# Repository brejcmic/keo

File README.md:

# B0B13KEO

- materiály, 
- prezentace

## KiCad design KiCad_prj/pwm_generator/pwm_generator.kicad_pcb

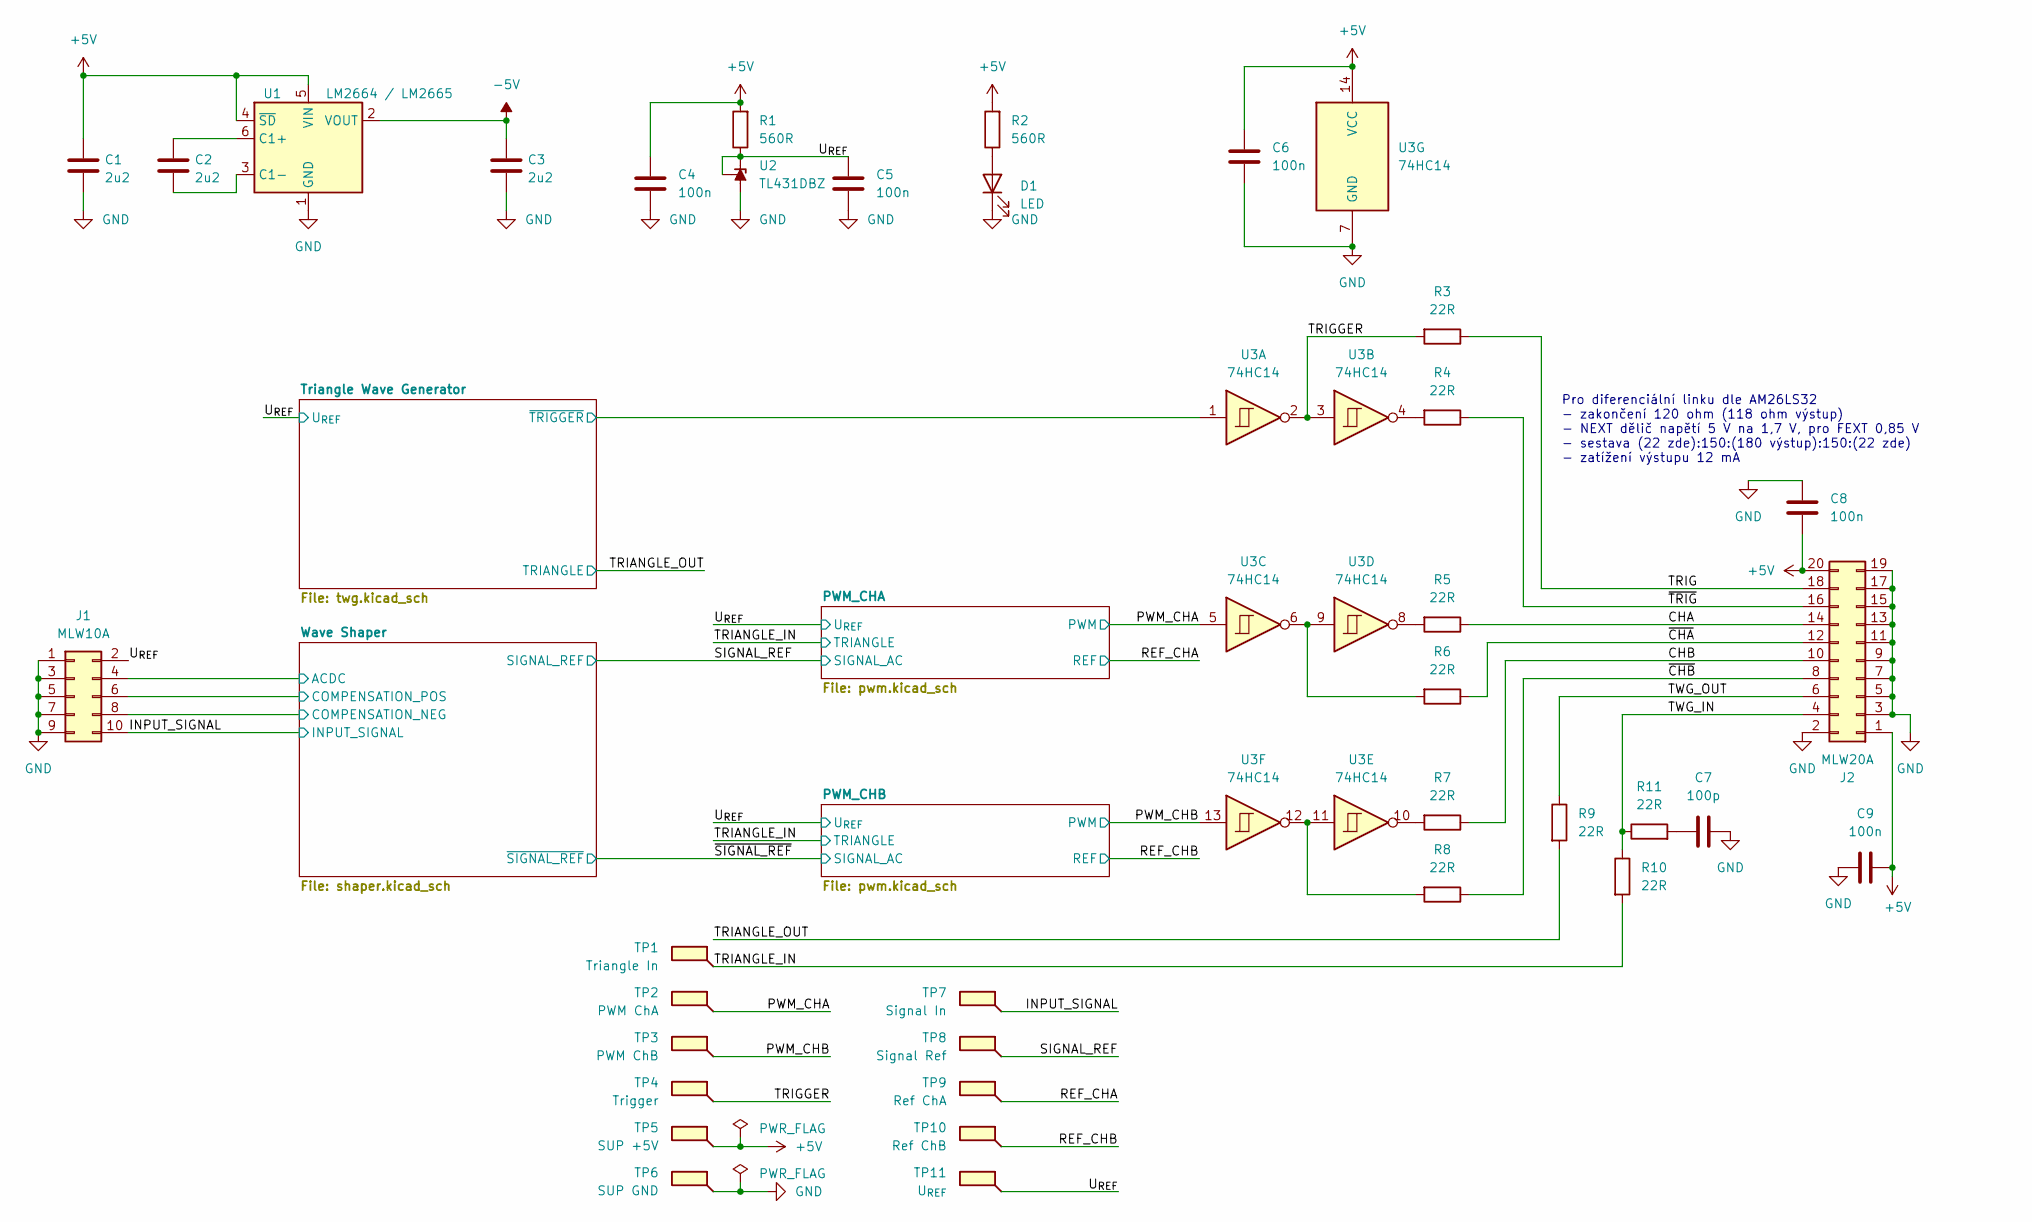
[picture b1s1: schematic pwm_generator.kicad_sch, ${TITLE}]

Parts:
C1, C2, C3: 2u2; C_0805_2012Metric; JLCPCB Part # C377773
C4, C5, C6, C8, C9: 100n; C_0805_2012Metric; JLCPCB Part # C49678
C7: 100p; C_0805_2012Metric; JLCPCB Part # C1790
D1: LED; LED_0805_2012Metric; JLCPCB Part # C84256
J1: MLW10A; IDC-Header_2x05_P2.54mm_Horizontal
J2: MLW20A; IDC-Header_2x10_P2.54mm_Horizontal
R1, R2: 560R; R_0805_2012Metric; JLCPCB Part # C28636
R3, R4, R5, R6, R7, R8, R9, R10, R11: 22R; R_0805_2012Metric; JLCPCB Part # C17561
TP1: Triangle In; TestPoint_Loop_D1.80mm_Drill1.0mm_Beaded
TP2: PWM ChA; TestPoint_Loop_D1.80mm_Drill1.0mm_Beaded
TP3: PWM ChB; TestPoint_Loop_D1.80mm_Drill1.0mm_Beaded
TP4: Trigger; TestPoint_Loop_D1.80mm_Drill1.0mm_Beaded
TP5: SUP +5V; TestPoint_Loop_D1.80mm_Drill1.0mm_Beaded
TP6: SUP GND; TestPoint_Loop_D1.80mm_Drill1.0mm_Beaded
TP7: Signal In; TestPoint_Loop_D1.80mm_Drill1.0mm_Beaded
TP8: Signal Ref; TestPoint_Loop_D1.80mm_Drill1.0mm_Beaded
TP9: Ref ChA; TestPoint_Loop_D1.80mm_Drill1.0mm_Beaded
TP10: Ref ChB; TestPoint_Loop_D1.80mm_Drill1.0mm_Beaded
TP11: U_{REF}; TestPoint_Loop_D1.80mm_Drill1.0mm_Beaded
U1: LM2664 / LM2665; SOT-23-6; JLCPCB Part # C840095
U2: TL431DBZ; SOT-23; JLCPCB Part # C181103
U3: 74HC14; SOIC-14_3.9x8.7mm_P1.27mm; JLCPCB Part # C5605

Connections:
+5V: C1.1, C4.2, C6.2, C8.2, C9.2, J2.1, J2.20, R1.2, R2.2, TP5.1 (1_1), U1.4 (~SD), U1.5 (VIN), U3.14 (VCC); also elsewhere on the board
-5V: C3.1, U1.2 (VOUT); also elsewhere on the board
/CHA: J2.14, R5.1
/CHB: J2.10, R7.1
/INPUT_SIGNAL: J1.10, TP7.1 (1_1); also elsewhere on the board
/PWM_CHA: TP2.1 (1_1), U3.5; also elsewhere on the board
/PWM_CHB: TP3.1 (1_1), U3.13; also elsewhere on the board
/REF_CHA: TP9.1 (1_1); also elsewhere on the board
/REF_CHB: TP10.1 (1_1); also elsewhere on the board
/SIGNAL_REF: TP8.1 (1_1); also elsewhere on the board
/TRIANGLE_IN: R10.2, TP1.1 (1_1); also elsewhere on the board
/TRIANGLE_OUT: R9.2; also elsewhere on the board
/TRIG: J2.18, R3.1
/TRIGGER: R3.2, TP4.1 (1_1), U3.2, U3.3
/TWG_IN: J2.4, R10.1, R11.1
/TWG_OUT: J2.6, R9.1
/Triangle Wave Generator/~TRIGGER: U3.1; also elsewhere on the board
/U_{REF}: C5.2, J1.2, R1.1, TP11.1 (1_1), U2.1 (K), U2.2 (REF); also elsewhere on the board
/Wave Shaper/ACDC: J1.4; also elsewhere on the board
/Wave Shaper/COMPENSATION_NEG: J1.8; also elsewhere on the board
/Wave Shaper/COMPENSATION_POS: J1.6; also elsewhere on the board
/~CHA: J2.12, R6.1
/~CHB: J2.8, R8.1
/~TRIG: J2.16, R4.1
GND: C1.2, C3.2, C4.1, C5.1, C6.1, C7.2, C8.1, C9.1, D1.1 (K), J1.1, J1.3, J1.5, J1.7, J1.9, J2.2, J2.3, J2.5, J2.7, J2.9, J2.11, J2.13, J2.15, J2.17, J2.19, TP6.1 (1_1), U1.1 (GND), U2.3 (A), U3.7 (GND); also elsewhere on the board
unnamed: C7.1, R11.2
unnamed: D1.2 (A), R2.1
unnamed: R4.2, U3.4
unnamed: R5.2, U3.8
unnamed: R6.2, U3.6, U3.9
unnamed: R7.2, U3.10
unnamed: R8.2, U3.11, U3.12
unnamed: C2.1, U1.6 (C1+)
unnamed: C2.2, U1.3 (C1-)

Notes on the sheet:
Pro diferenciální linku dle AM26LS32 - zakončení 120 ohm (118 ohm výstup) - NEXT dělič napětí 5 V na 1,7 V, pro FEXT 0,85 V - sestava (22 zde):150:(180 výstup):150:(22 zde) - zatížení výstupu 12 mA

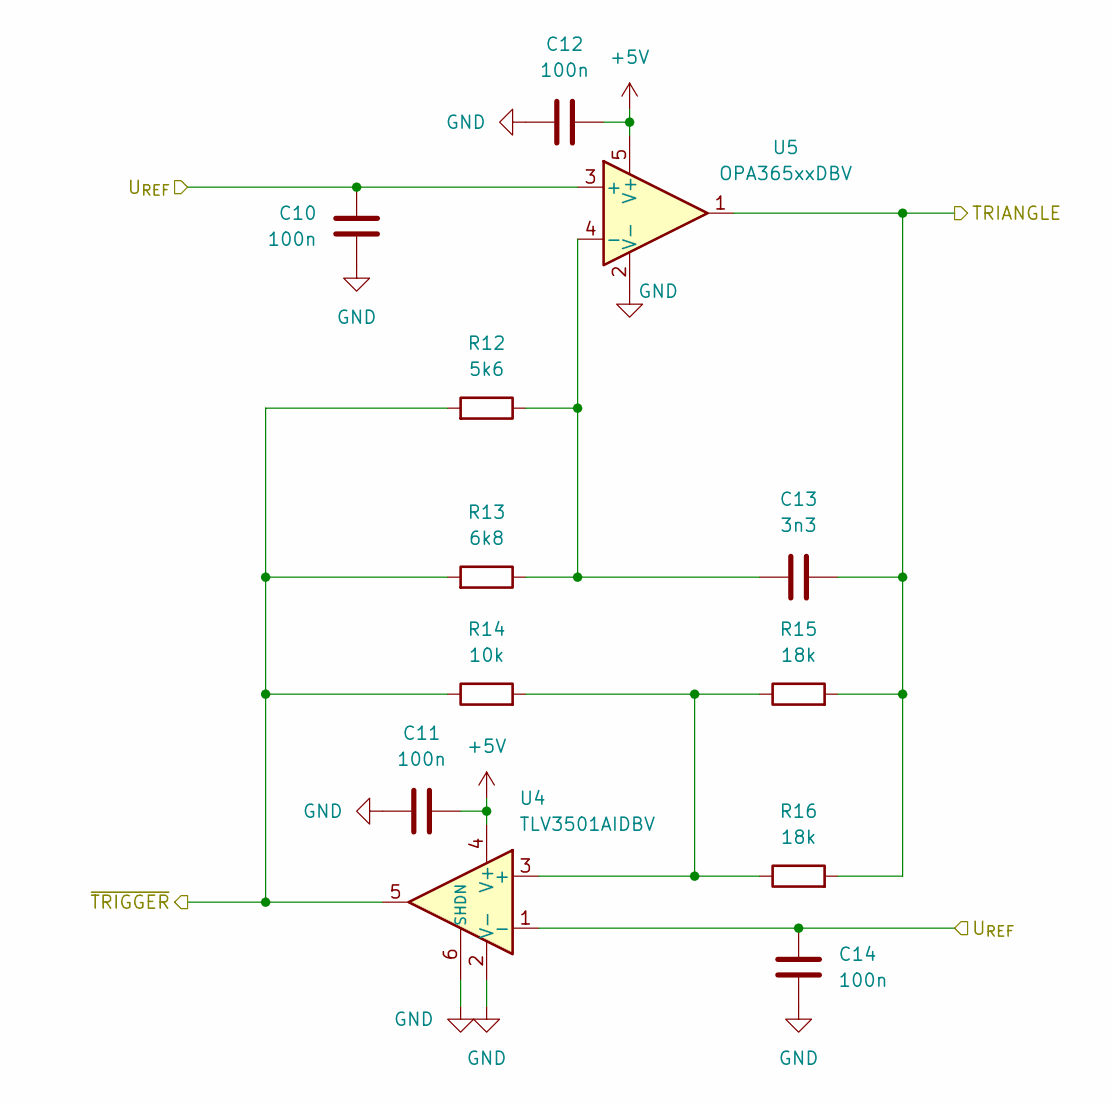
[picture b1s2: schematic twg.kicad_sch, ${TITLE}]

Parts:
C10, C11, C12, C14: 100n; C_0805_2012Metric; JLCPCB Part # C49678
C13: 3n3; C_0805_2012Metric; JLCPCB Part # C7467177
R12: 5k6; R_0805_2012Metric; JLCPCB Part # C4382
R13: 6k8; R_0805_2012Metric; JLCPCB Part # C17772
R14: 10k; R_0805_2012Metric; JLCPCB Part # C17414
R15, R16: 18k; R_0805_2012Metric; JLCPCB Part # C17506
U4: TLV3501AIDBV; SOT-23-6; JLCPCB Part # C193413
U5: OPA365xxDBV; SOT-23-5; JLCPCB Part # C96626

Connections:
+5V: C11.2, C12.2, U4.4 (V+), U5.5 (V+); also elsewhere on the board
/TRIANGLE_OUT: C13.2, R15.2, R16.2, U5.1; also elsewhere on the board
/Triangle Wave Generator/~TRIGGER: R12.2, R13.2, R14.1, U4.5; also elsewhere on the board
/U_{REF}: C10.2, C14.2, U4.1 (-), U5.3 (+); also elsewhere on the board
GND: C10.1, C11.1, C12.1, C14.1, U4.2 (V-), U4.6 (SHDN), U5.2 (V-); also elsewhere on the board
unnamed: R14.2, R15.1, R16.1, U4.3 (+)
unnamed: C13.1, R12.1, R13.1, U5.4 (-)

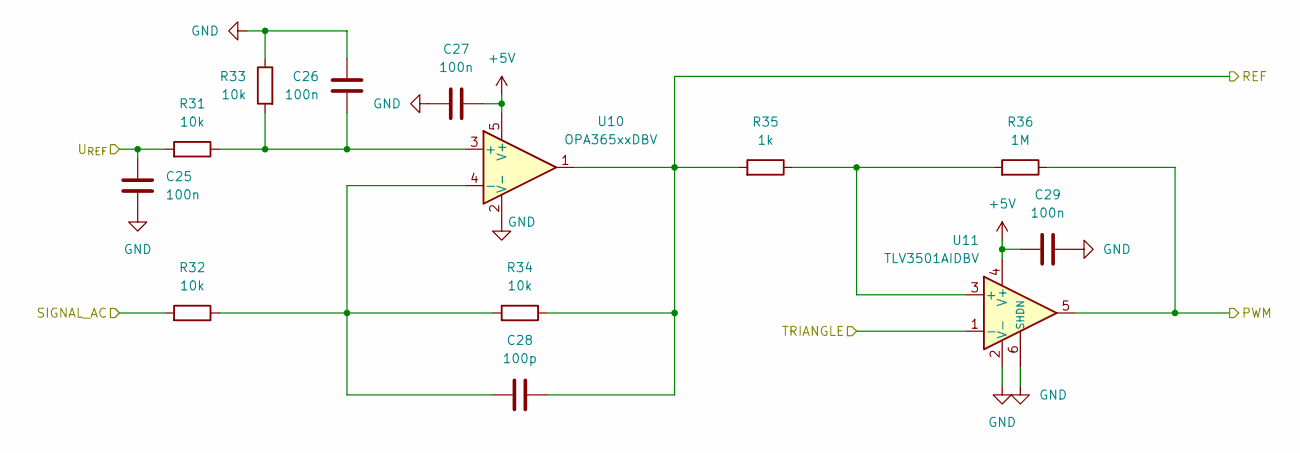
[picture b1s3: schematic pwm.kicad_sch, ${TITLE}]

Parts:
C25, C26, C27, C29: 100n; C_0805_2012Metric; JLCPCB Part # C49678
C28: 100p; C_0805_2012Metric; JLCPCB Part # C1790
R31, R32, R33, R34: 10k; R_0805_2012Metric; JLCPCB Part # C17414
R35: 1k; R_0805_2012Metric; JLCPCB Part # C17513
R36: 1M; R_0805_2012Metric; JLCPCB Part # C17514
U10: OPA365xxDBV; SOT-23-5; JLCPCB Part # C96626
U11: TLV3501AIDBV; SOT-23-6; JLCPCB Part # C193413

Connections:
+5V: C27.2, C29.2, U10.5 (V+), U11.4 (V+); also elsewhere on the board
/PWM_CHA: R36.1, U11.5; also elsewhere on the board
/REF_CHA: C28.2, R34.1, R35.2, U10.1; also elsewhere on the board
/SIGNAL_REF: R32.2; also elsewhere on the board
/TRIANGLE_IN: U11.1 (-); also elsewhere on the board
/U_{REF}: C25.2, R31.2; also elsewhere on the board
GND: C25.1, C26.1, C27.1, C29.1, R33.1, U10.2 (V-), U11.2 (V-), U11.6 (SHDN); also elsewhere on the board
unnamed: C26.2, R31.1, R33.2, U10.3 (+)
unnamed: C28.1, R32.1, R34.2, U10.4 (-)
unnamed: R35.1, R36.2, U11.3 (+)

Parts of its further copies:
C30, C31, C32, C34: 100n; C_0805_2012Metric; JLCPCB Part # C49678
C33: 100p; C_0805_2012Metric; JLCPCB Part # C1790
R37, R38, R39, R40: 10k; R_0805_2012Metric; JLCPCB Part # C17414
R41: 1k; R_0805_2012Metric; JLCPCB Part # C17513
R42: 1M; R_0805_2012Metric; JLCPCB Part # C17514
U12: OPA365xxDBV; SOT-23-5; JLCPCB Part # C96626
U13: TLV3501AIDBV; SOT-23-6; JLCPCB Part # C193413

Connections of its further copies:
+5V: C32.2, C34.2, U12.5 (V+), U13.4 (V+); also elsewhere on the board
/PWM_CHB: R42.1, U13.5; also elsewhere on the board
/REF_CHB: C33.2, R40.1, R41.2, U12.1; also elsewhere on the board
/TRIANGLE_IN: U13.1 (-); also elsewhere on the board
/U_{REF}: C30.2, R37.2; also elsewhere on the board
/~SIGNAL_REF: R38.2; also elsewhere on the board
GND: C30.1, C31.1, C32.1, C34.1, R39.1, U12.2 (V-), U13.2 (V-), U13.6 (SHDN); also elsewhere on the board
unnamed: C31.2, R37.1, R39.2, U12.3 (+)
unnamed: C33.1, R38.1, R40.2, U12.4 (-)
unnamed: R41.1, R42.2, U13.3 (+)

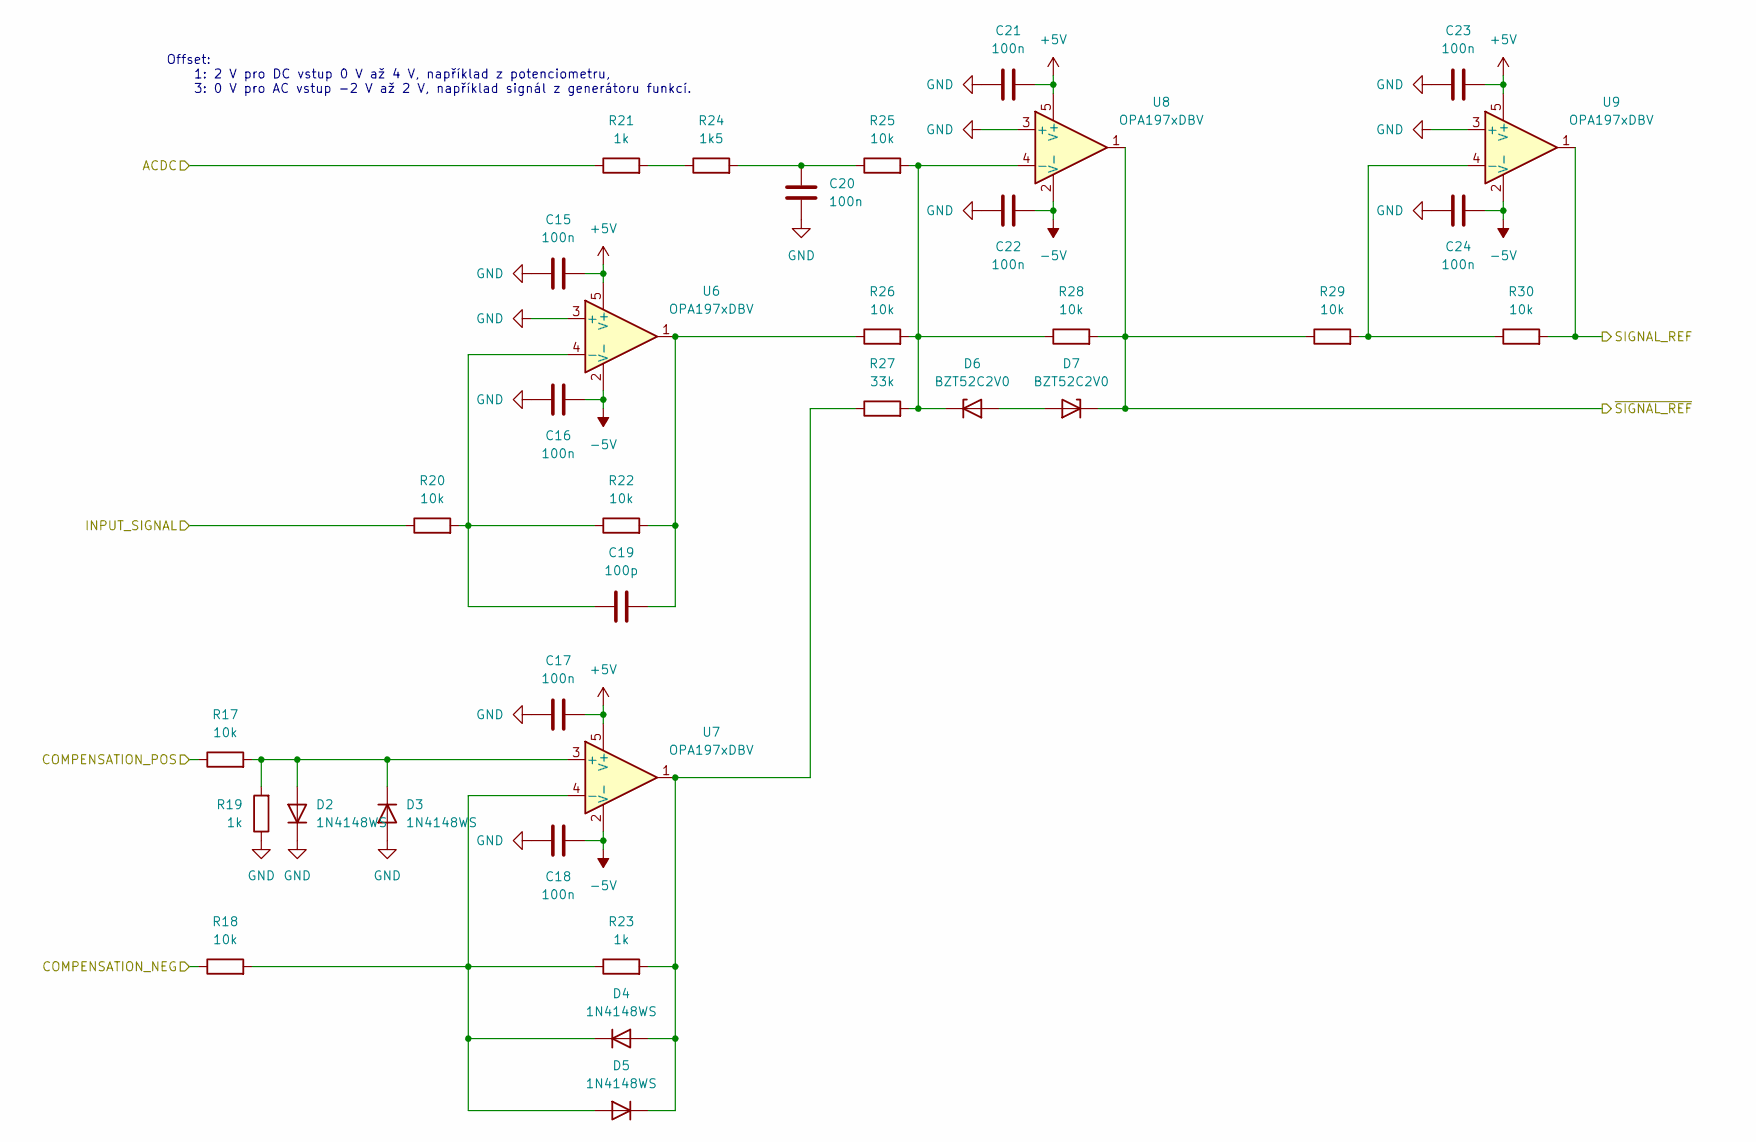
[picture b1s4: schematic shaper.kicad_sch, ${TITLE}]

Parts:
C15, C16, C17, C18, C20, C21, C22, C23, C24: 100n; C_0805_2012Metric; JLCPCB Part # C49678
C19: 100p; C_0805_2012Metric; JLCPCB Part # C1790
D2, D3, D4, D5: 1N4148WS; D_SOD-323; JLCPCB Part # C2128
D6, D7: BZT52C2V0; D_SOD-123F; JLCPCB Part # C41410795
R17, R18, R20, R22, R25, R26, R28, R29, R30: 10k; R_0805_2012Metric; JLCPCB Part # C17414
R19, R21, R23: 1k; R_0805_2012Metric; JLCPCB Part # C17513
R24: 1k5; R_0805_2012Metric; JLCPCB Part # C4310
R27: 33k; R_0805_2012Metric; JLCPCB Part # C17633
U6, U7, U8, U9: OPA197xDBV; SOT-23-5; JLCPCB Part # C221351

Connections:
+5V: C15.2, C17.2, C21.2, C23.2, U6.5 (V+), U7.5 (V+), U8.5 (V+), U9.5 (V+); also elsewhere on the board
-5V: C16.2, C18.2, C22.2, C24.2, U6.2 (V-), U7.2 (V-), U8.2 (V-), U9.2 (V-); also elsewhere on the board
/INPUT_SIGNAL: R20.1; also elsewhere on the board
/SIGNAL_REF: R30.2, U9.1; also elsewhere on the board
/Wave Shaper/ACDC: R21.1; also elsewhere on the board
/Wave Shaper/COMPENSATION_NEG: R18.1; also elsewhere on the board
/Wave Shaper/COMPENSATION_POS: R17.1; also elsewhere on the board
/~SIGNAL_REF: D7.1 (K), R28.2, R29.1, U8.1; also elsewhere on the board
GND: C15.1, C16.1, C17.1, C18.1, C20.1, C21.1, C22.1, C23.1, C24.1, D2.1 (K), D3.2 (A), R19.1, U6.3 (+), U8.3 (+), U9.3 (+); also elsewhere on the board
unnamed: C19.2, R22.2, R26.1, U6.1
unnamed: C20.2, R24.2, R25.1
unnamed: D2.2 (A), D3.1 (K), R17.2, R19.2, U7.3 (+)
unnamed: D4.2 (A), D5.1 (K), R23.2, R27.1, U7.1
unnamed: D4.1 (K), D5.2 (A), R18.2, R23.1, U7.4 (-)
unnamed: D6.2 (A), D7.2 (A)
unnamed: D6.1 (K), R25.2, R26.2, R27.2, R28.1, U8.4 (-)
unnamed: R21.2, R24.1
unnamed: C19.1, R20.2, R22.1, U6.4 (-)
unnamed: R29.2, R30.1, U9.4 (-)

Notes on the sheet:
Offset: 1: 2 V pro DC vstup 0 V až 4 V, například z potenciometru, 3: 0 V pro AC vstup -2 V až 2 V, například signál z generátoru funkcí.

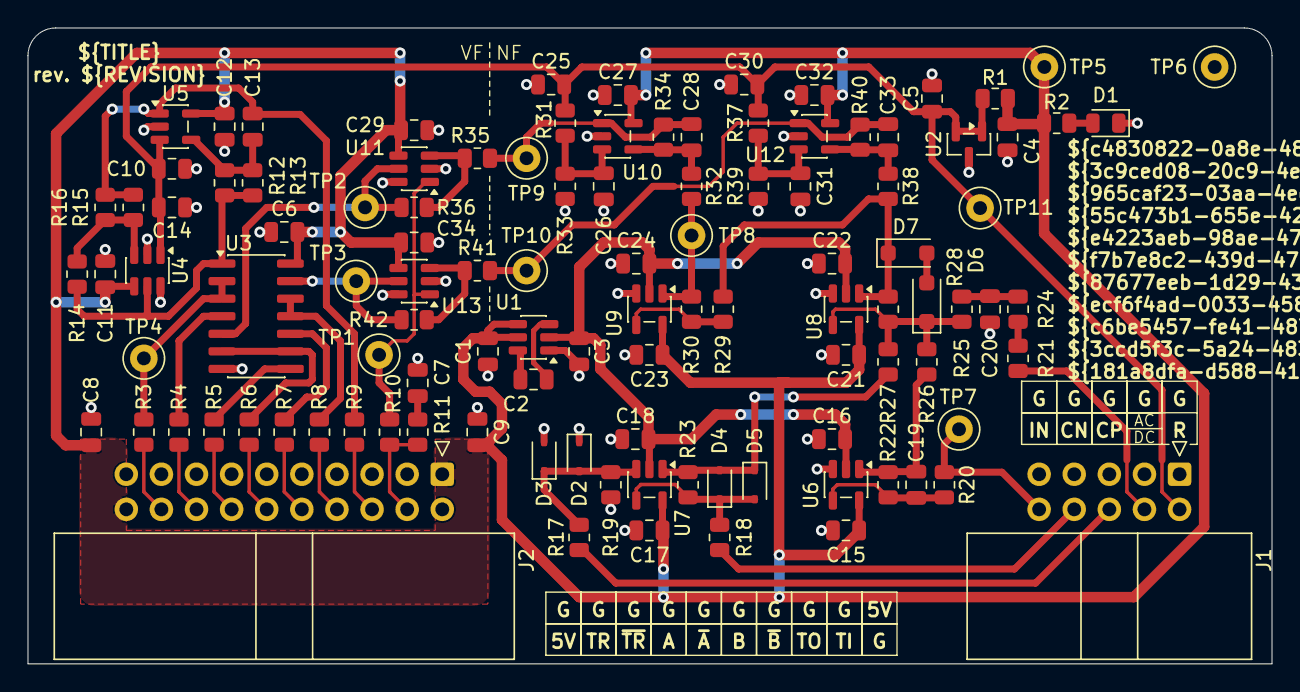
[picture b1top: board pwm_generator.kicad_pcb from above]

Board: 2 copper layers, 90.0 x 46.0 mm, 109 parts (0 on the bottom side), 53 nets.

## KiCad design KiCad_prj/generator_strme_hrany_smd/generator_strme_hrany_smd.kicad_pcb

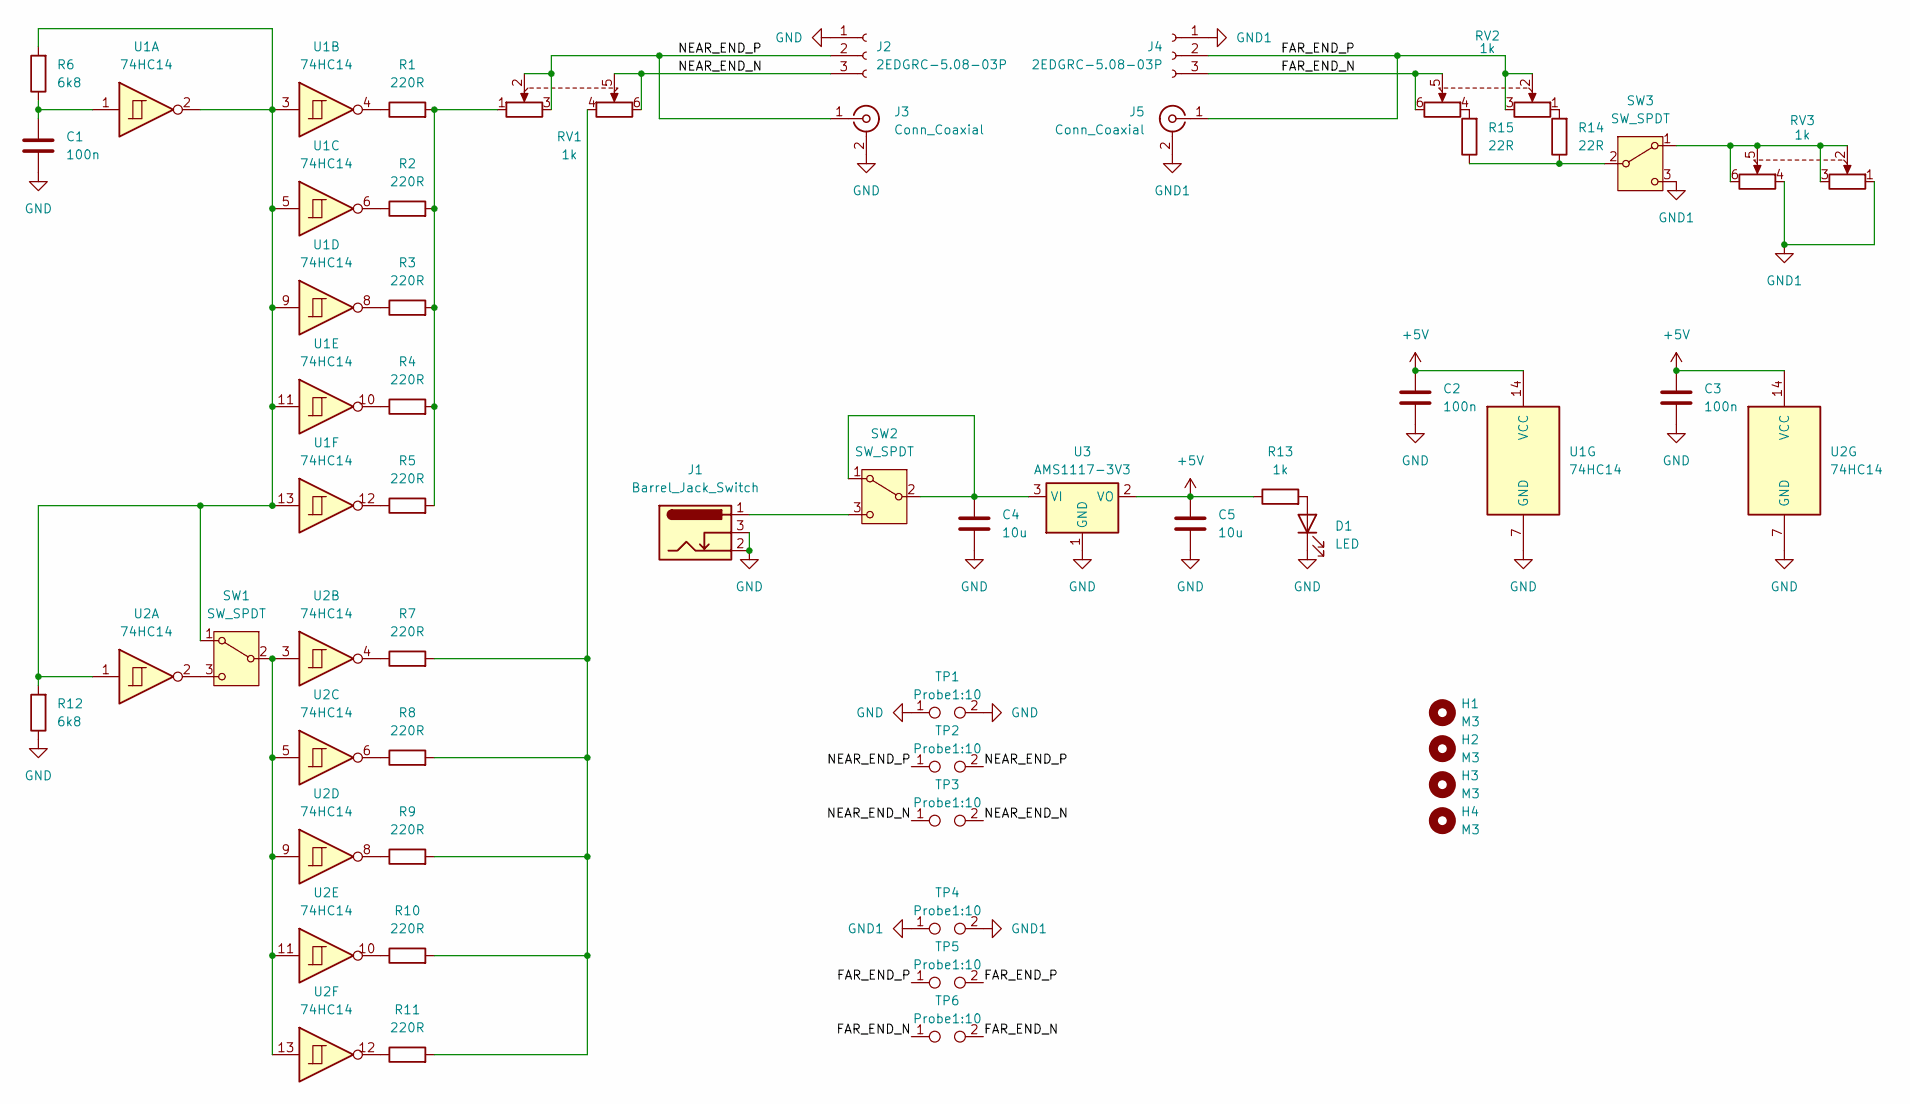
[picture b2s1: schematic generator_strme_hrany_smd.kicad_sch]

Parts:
C1, C2, C3: 100n; C_0805_2012Metric
C4, C5: 10u; C_0805_2012Metric
D1: LED; LED_0805_2012Metric
H1, H2, H3, H4: M3; MountingHole_3.2mm_M3_ISO7380
J1: Barrel_Jack_Switch; BarrelJack_GCT_DCJ200-10-A_Horizontal
J2, J4: 2EDGRC-5.08-03P; PhoenixContact_MSTBA_2,5_3-G-5,08_1x03_P5.08mm_Horizontal
J3, J5: Conn_Coaxial; BNC_Amphenol_B6252HB-NPP3G-50_Horizontal
R1, R2, R3, R4, R5, R7, R8, R9, R10, R11: 220R; R_0805_2012Metric
R6, R12: 6k8; R_0805_2012Metric
R13: 1k; R_0805_2012Metric
R14, R15: 22R; R_0805_2012Metric
RV1, RV2, RV3: 1k; Potentiometer_Alpha_RD902F-40-00D_Dual_Vertical
SW1, SW2, SW3: SW_SPDT; KLS7-SS02-12F20
TP1, TP2, TP3, TP4, TP5, TP6: Probe1:10; TestPoint_2Pads_Pitch2.54mm_Drill0.8mm
U1, U2: 74HC14; DIP-14_W7.62mm_LongPads
U3: AMS1117-3V3; SOT-223-3_TabPin2

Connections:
+5V: C2.1, C3.1, C5.1, R13.1, U1.14 (VCC), U2.14 (VCC), U3.2 (VO)
/FAR_END_N: J4.3, RV2.5, RV2.6, TP6.1, TP6.2
/FAR_END_P: J4.2, J5.1 (In), RV2.2, RV2.3, TP5.1, TP5.2
/NEAR_END_N: J2.3, RV1.5, RV1.6, TP3.1, TP3.2
/NEAR_END_P: J2.2, J3.1 (In), RV1.2, RV1.3, TP2.1, TP2.2
GND: C1.2, C2.2, C3.2, C4.2, C5.2, D1.1 (K), J1.2, J1.3, J2.1, J3.2 (Ext), R12.1, TP1.1, TP1.2, U1.7 (GND), U2.7 (GND), U3.1 (GND)
GND1: J4.1, J5.2 (Ext), RV3.1, RV3.4, SW3.3 (C), TP4.1, TP4.2
unnamed: C1.1, R6.1, U1.1
unnamed: D1.2 (A), R13.2
unnamed: R1.1, U1.4
unnamed: R1.2, R2.2, R3.2, R4.2, R5.2, RV1.1
unnamed: R2.1, U1.6
unnamed: R3.1, U1.8
unnamed: R4.1, U1.10
unnamed: R5.1, U1.12
unnamed: R7.1, U2.4
unnamed: R8.1, U2.6
unnamed: R9.1, U2.8
unnamed: R10.1, U2.10
unnamed: R7.2, R8.2, R9.2, R10.2, R11.2, RV1.4
unnamed: R11.1, U2.12
unnamed: R14.2, RV2.1
unnamed: R15.2, RV2.4
unnamed: R6.2, R12.2, SW1.1 (A), U1.2, U1.3, U1.5, U1.9, U1.11, U1.13, U2.1
unnamed: SW1.2 (B), U2.3, U2.5, U2.9, U2.11, U2.13
unnamed: SW1.3 (C), U2.2
unnamed: C4.1, SW2.1 (A), SW2.2 (B), U3.3 (VI)
unnamed: J1.1, SW2.3 (C)
unnamed: RV3.2, RV3.3, RV3.5, RV3.6, SW3.1 (A)
unnamed: R14.1, R15.1, SW3.2 (B)

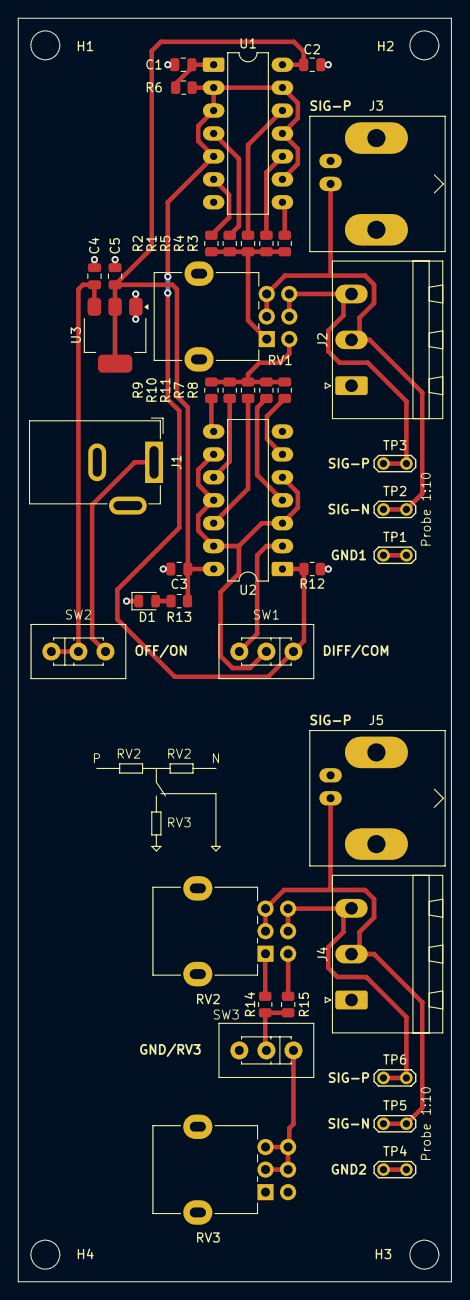
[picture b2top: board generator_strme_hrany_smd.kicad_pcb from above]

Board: 2 copper layers, 48.0 x 140.0 mm, 45 parts (0 on the bottom side), 30 nets.

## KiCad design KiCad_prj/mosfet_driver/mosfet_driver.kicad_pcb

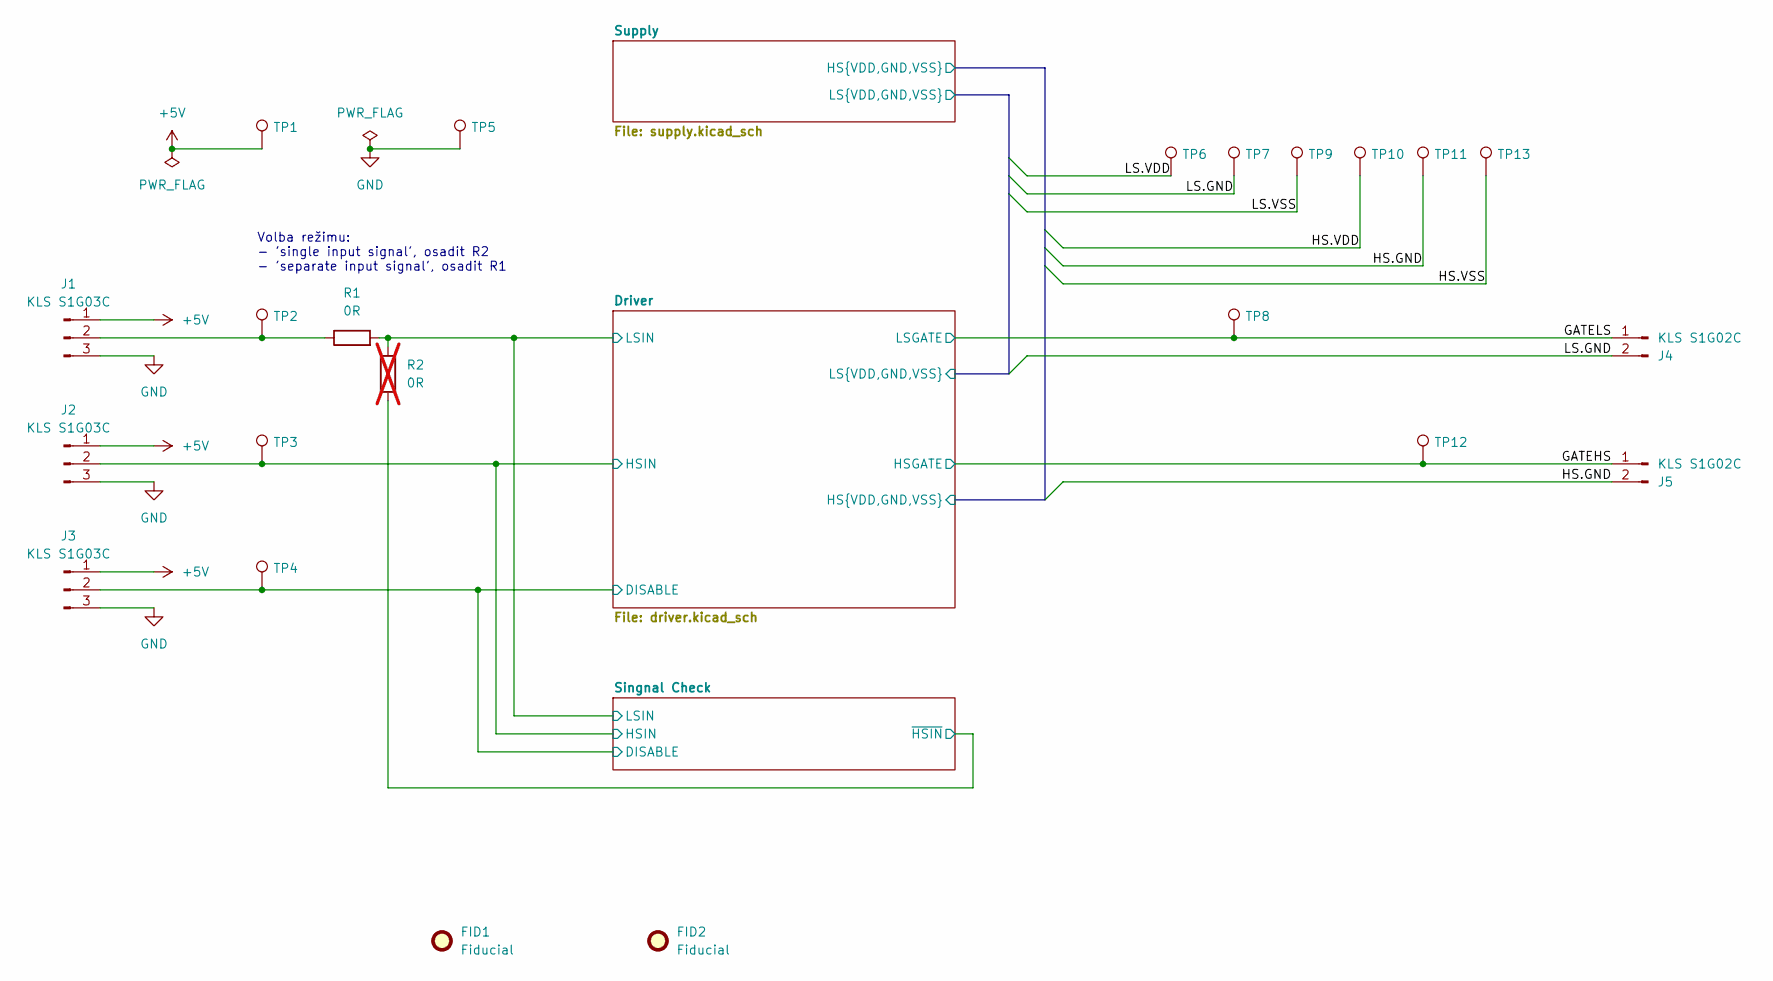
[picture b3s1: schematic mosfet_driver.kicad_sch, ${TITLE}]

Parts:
FID1, FID2: Fiducial; Fiducial_0.5mm_Mask1mm
J1, J2, J3: KLS S1G03C; PinHeader_1x03_P2.54mm_Horizontal
J4, J5: KLS S1G02C; PinHeader_1x02_P2.54mm_Horizontal
R1: 0R; R_0805_2012Metric; JLCPCB Part # C17477
R2: 0R; R_0805_2012Metric; JLCPCB Part # C17477; not fitted
TP1, TP2, TP3, TP4, TP5, TP6, TP7, TP8, TP9, TP10, TP11, TP12, TP13: D1MM; TestPoint_Loop_D2.50mm_Drill1.0mm

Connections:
+5V: J1.1, J2.1, J3.1, TP1.1; also elsewhere on the board
/Driver/DISABLE: J3.2, TP4.1; also elsewhere on the board
/Driver/HS.GND: J5.2, TP11.1; also elsewhere on the board
/Driver/HS.VDD: TP10.1; also elsewhere on the board
/Driver/HS.VSS: TP13.1; also elsewhere on the board
/Driver/HSIN: J2.2, TP3.1; also elsewhere on the board
/Driver/LS.GND: J4.2, TP7.1; also elsewhere on the board
/Driver/LS.VDD: TP6.1; also elsewhere on the board
/Driver/LS.VSS: TP9.1; also elsewhere on the board
/Driver/LSIN: R1.2, R2.1; also elsewhere on the board
/GATEHS: J5.1, TP12.1; also elsewhere on the board
/GATELS: J4.1, TP8.1; also elsewhere on the board
/Singnal Check/~HSIN: R2.2; also elsewhere on the board
GND: J1.3, J2.3, J3.3, TP5.1; also elsewhere on the board
unnamed: J1.2, R1.1, TP2.1

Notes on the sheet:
Volba režimu: - 'single input signal', osadit R2 - 'separate input signal', osadit R1

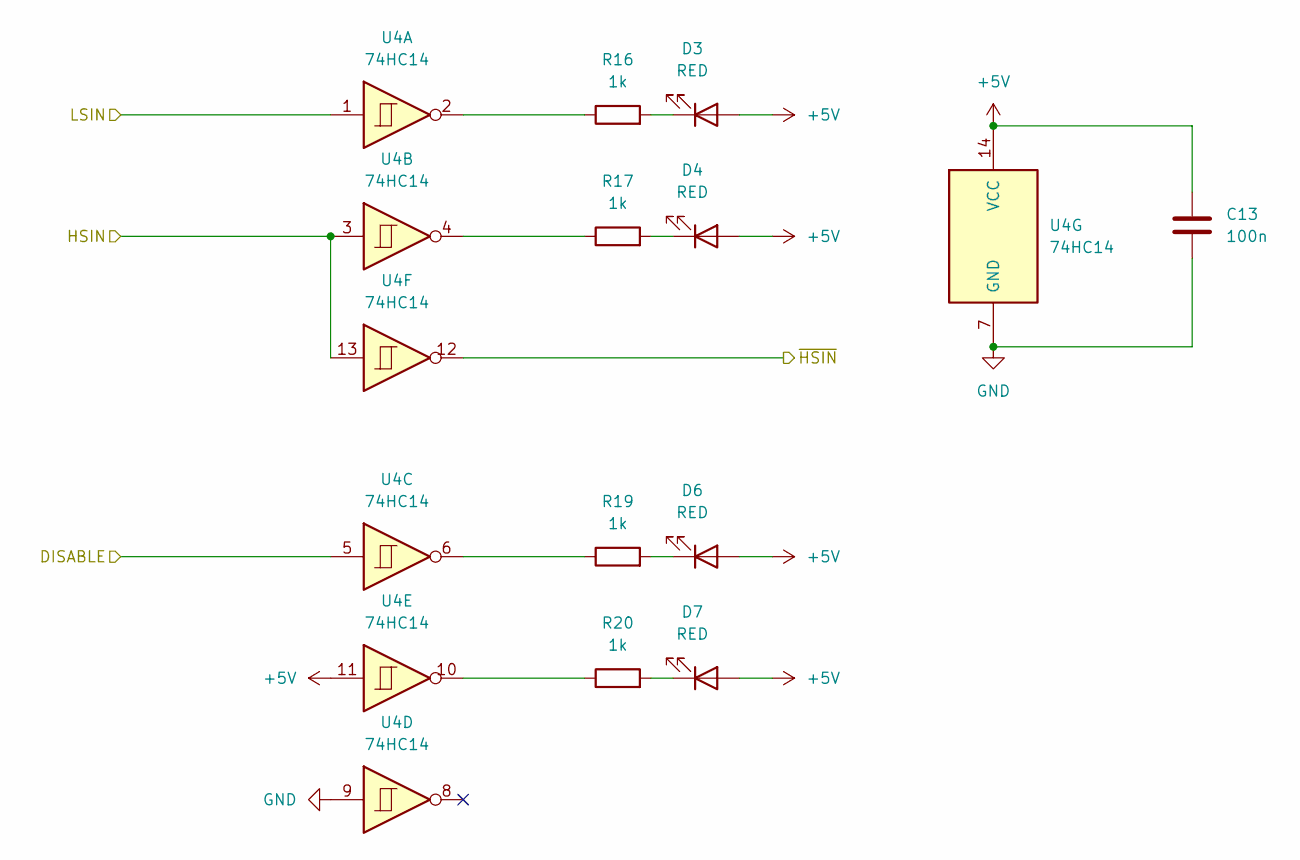
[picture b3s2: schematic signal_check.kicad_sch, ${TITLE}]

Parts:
C13: 100n; C_0805_2012Metric; JLCPCB Part # C28233
D3, D4, D6, D7: RED; LED_0805_2012Metric; JLCPCB Part # C84256
R16, R17, R19, R20: 1k; R_0805_2012Metric; JLCPCB Part # C17513
U4: 74HC14; SOIC-14_3.9x8.7mm_P1.27mm; JLCPCB Part # C5605

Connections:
+5V: C13.1, D3.2 (A), D4.2 (A), D6.2 (A), D7.2 (A), U4.11, U4.14 (VCC); also elsewhere on the board
/Driver/DISABLE: U4.5; also elsewhere on the board
/Driver/HSIN: U4.3, U4.13; also elsewhere on the board
/Driver/LSIN: U4.1; also elsewhere on the board
/Singnal Check/~HSIN: U4.12; also elsewhere on the board
GND: C13.2, U4.7 (GND), U4.9; also elsewhere on the board
unnamed: D3.1 (K), R16.2
unnamed: D4.1 (K), R17.2
unnamed: D6.1 (K), R19.2
unnamed: D7.1 (K), R20.2
unnamed: R16.1, U4.2
unnamed: R17.1, U4.4
unnamed: R19.1, U4.6
unnamed: R20.1, U4.10

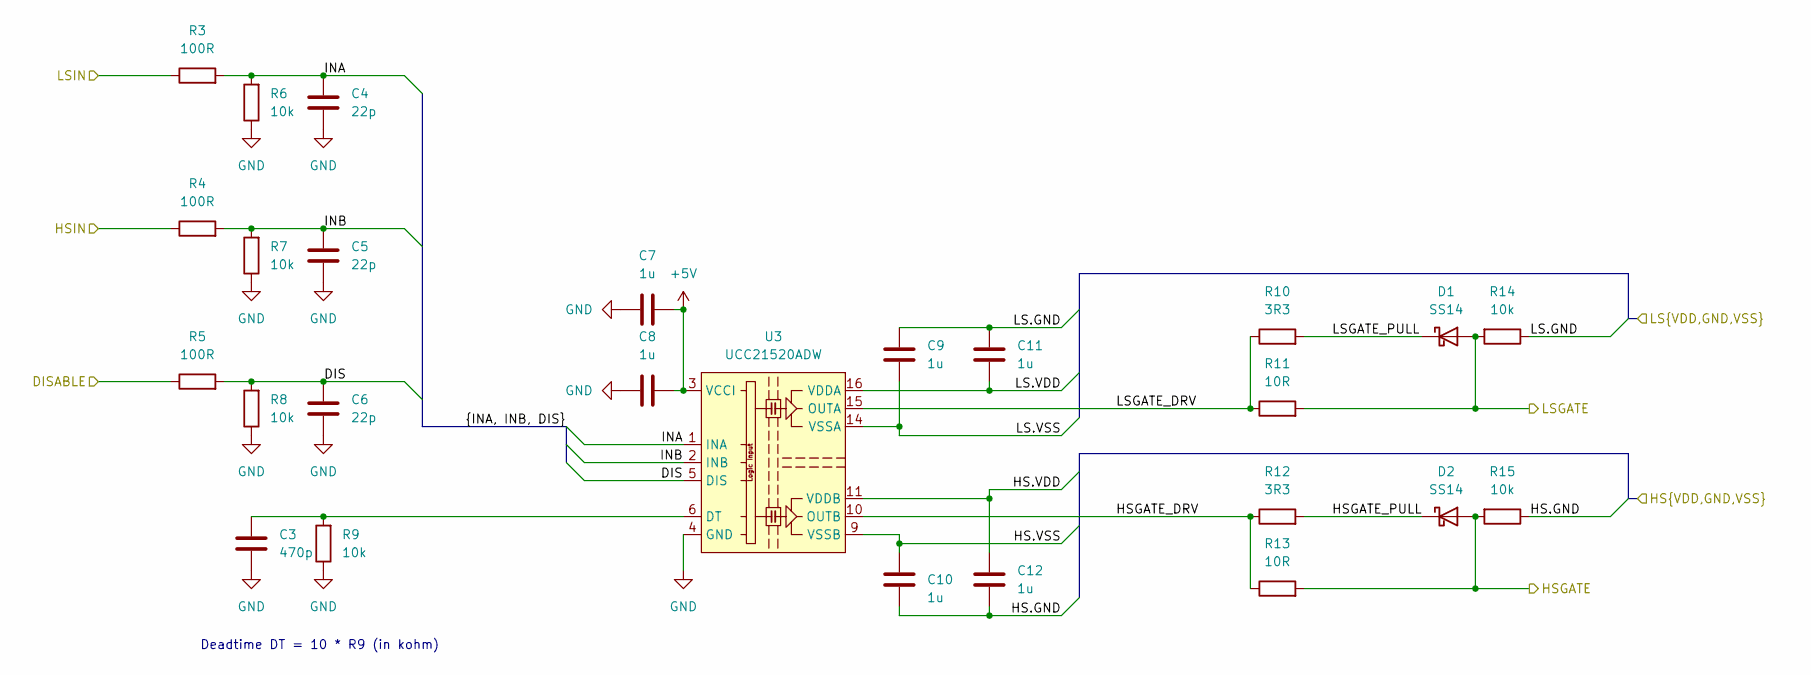
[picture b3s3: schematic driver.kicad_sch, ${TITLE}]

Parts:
C3: 470p; C_0805_2012Metric; JLCPCB Part # C1743
C4, C5, C6: 22p; C_0805_2012Metric; JLCPCB Part # C1804
C7, C8, C9, C10, C11, C12: 1u; C_0805_2012Metric; JLCPCB Part # C28323
D1, D2: SS14; D_SMA; JLCPCB Part # C2480
R3, R4, R5: 100R; R_0805_2012Metric; JLCPCB Part # C17408
R6, R7, R8, R9, R14, R15: 10k; R_0805_2012Metric; JLCPCB Part # C17414
R10, R12: 3R3; R_0805_2012Metric; JLCPCB Part # C16257
R11, R13: 10R; R_0805_2012Metric; JLCPCB Part # C17415
U3: UCC21520ADW; SOIC-16W_7.5x10.3mm_P1.27mm; JLCPCB Part # C2863027

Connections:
+5V: C7.1, C8.1, U3.3 (VCCI), U3.8 (VCCI); also elsewhere on the board
/Driver/DIS: C6.1, R5.2, R8.2, U3.5 (DIS)
/Driver/DISABLE: R5.1; also elsewhere on the board
/Driver/HS.GND: C10.2, C12.2, R15.1; also elsewhere on the board
/Driver/HS.VDD: C12.1, U3.11 (VDDB); also elsewhere on the board
/Driver/HS.VSS: C10.1, U3.9 (VSSB); also elsewhere on the board
/Driver/HSGATE_DRV: R12.1, R13.1, U3.10 (OUTB)
/Driver/HSGATE_PULL: D2.1 (K), R12.2
/Driver/HSIN: R4.1; also elsewhere on the board
/Driver/INA: C4.1, R3.2, R6.2, U3.1 (INA)
/Driver/INB: C5.1, R4.2, R7.2, U3.2 (INB)
/Driver/LS.GND: C9.2, C11.2, R14.1; also elsewhere on the board
/Driver/LS.VDD: C11.1, U3.16 (VDDA); also elsewhere on the board
/Driver/LS.VSS: C9.1, U3.14 (VSSA); also elsewhere on the board
/Driver/LSGATE_DRV: R10.1, R11.1, U3.15 (OUTA)
/Driver/LSGATE_PULL: D1.1 (K), R10.2
/Driver/LSIN: R3.1; also elsewhere on the board
/GATEHS: D2.2 (A), R13.2, R15.2; also elsewhere on the board
/GATELS: D1.2 (A), R11.2, R14.2; also elsewhere on the board
GND: C3.2, C4.2, C5.2, C6.2, C7.2, C8.2, R6.1, R7.1, R8.1, R9.1, U3.4 (GND); also elsewhere on the board
unnamed: C3.1, R9.2, U3.6 (DT)

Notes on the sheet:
Deadtime DT = 10 * R9 (in kohm)
